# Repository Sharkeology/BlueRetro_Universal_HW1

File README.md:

# BlueRetro Universal HW1
A basic board meant to be used with the [BlueRetro project](https://github.com/darthcloud/BlueRetro) to simplify basic “HW1” internal installation in various supported consoles. Including onboard level shifting 3.3v regulation for consoles which don’t provide it.

### Bill of Materials
- [ESP-WROOM-32 Module](https://www.espressif.com/sites/default/files/documentation/esp32-wroom-32_datasheet_en.pdf)
- 2 x [TXS0108E 8-Bit Bi-directional, Level-Shifting, Voltage Translator](https://www.ti.com/lit/ds/symlink/txs0108e.pdf)
- 0805 1kΩ Pull-up Resistor for TXS0108E
- [AMS1117-3.3 3.3V 1A Low Dropout Voltage Regulator](http://www.advanced-monolithic.com/pdf/ds1117.pdf)
- 2 x 0805 Decoupling Capacitors for AMS1117 (I'm unsure of appropriate values, 1μF is what I used)

TXS0108EPWR Footprint and symbol courtesy of [SnapEDA](https://www.snapeda.com/parts/TXS0108EPWR/Texas%20Instruments/view-part/),
BlueRetro logo created by [HumbleBazooka](https://twitter.com/humblebazooka).

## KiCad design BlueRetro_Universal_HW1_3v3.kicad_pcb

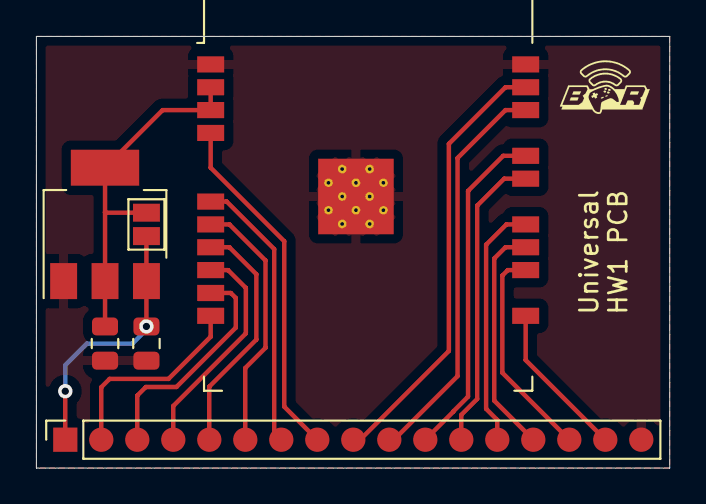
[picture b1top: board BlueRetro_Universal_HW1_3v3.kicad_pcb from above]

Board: 2 copper layers, 35.2 x 24.0 mm, 6 parts (0 on the bottom side), 18 nets.

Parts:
C1, C2: 1uF; C_0805_2012Metric
J1: Conn_01x17; PinSocket_1x17_P2.00mm_Vertical
JP1: SolderJumper_2_Open; SolderJumper-2_P1.3mm_Open_Pad1.0x1.5mm
U1: AMS1117-3.3; SOT-223-3_TabPin2
U2: ESP32-WROOM-32

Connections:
+3V3: C2.1, JP1.2 (B), U1.2 (VO), U2.2 (VDD), U2.3 (EN)
+5V: C1.1, J1.1, JP1.1 (A), U1.3 (VI)
GND: C1.2, C2.2, J1.17, U1.1 (GND), U2.1 (GND), U2.38 (GND), U2.39 (GND)
IO3: J1.11, U2.34 (RXD0/IO3)
IO5: J1.15, U2.29 (IO5)
IO16: J1.16, U2.27 (IO16)
IO18: J1.14, U2.30 (IO18)
IO19: J1.13, U2.31 (IO19)
IO21: J1.12, U2.33 (IO21)
IO22: J1.10, U2.36 (IO22)
IO23: J1.9, U2.37 (IO23)
IO25: J1.4, U2.10 (IO25)
IO26: J1.3, U2.11 (IO26)
IO27: J1.2, U2.12 (IO27)
IO32: J1.6, U2.8 (IO32)
IO33: J1.5, U2.9 (IO33)
IO35: J1.7, U2.7 (IO35)
IO36: J1.8, U2.4 (SENSOR_VP)

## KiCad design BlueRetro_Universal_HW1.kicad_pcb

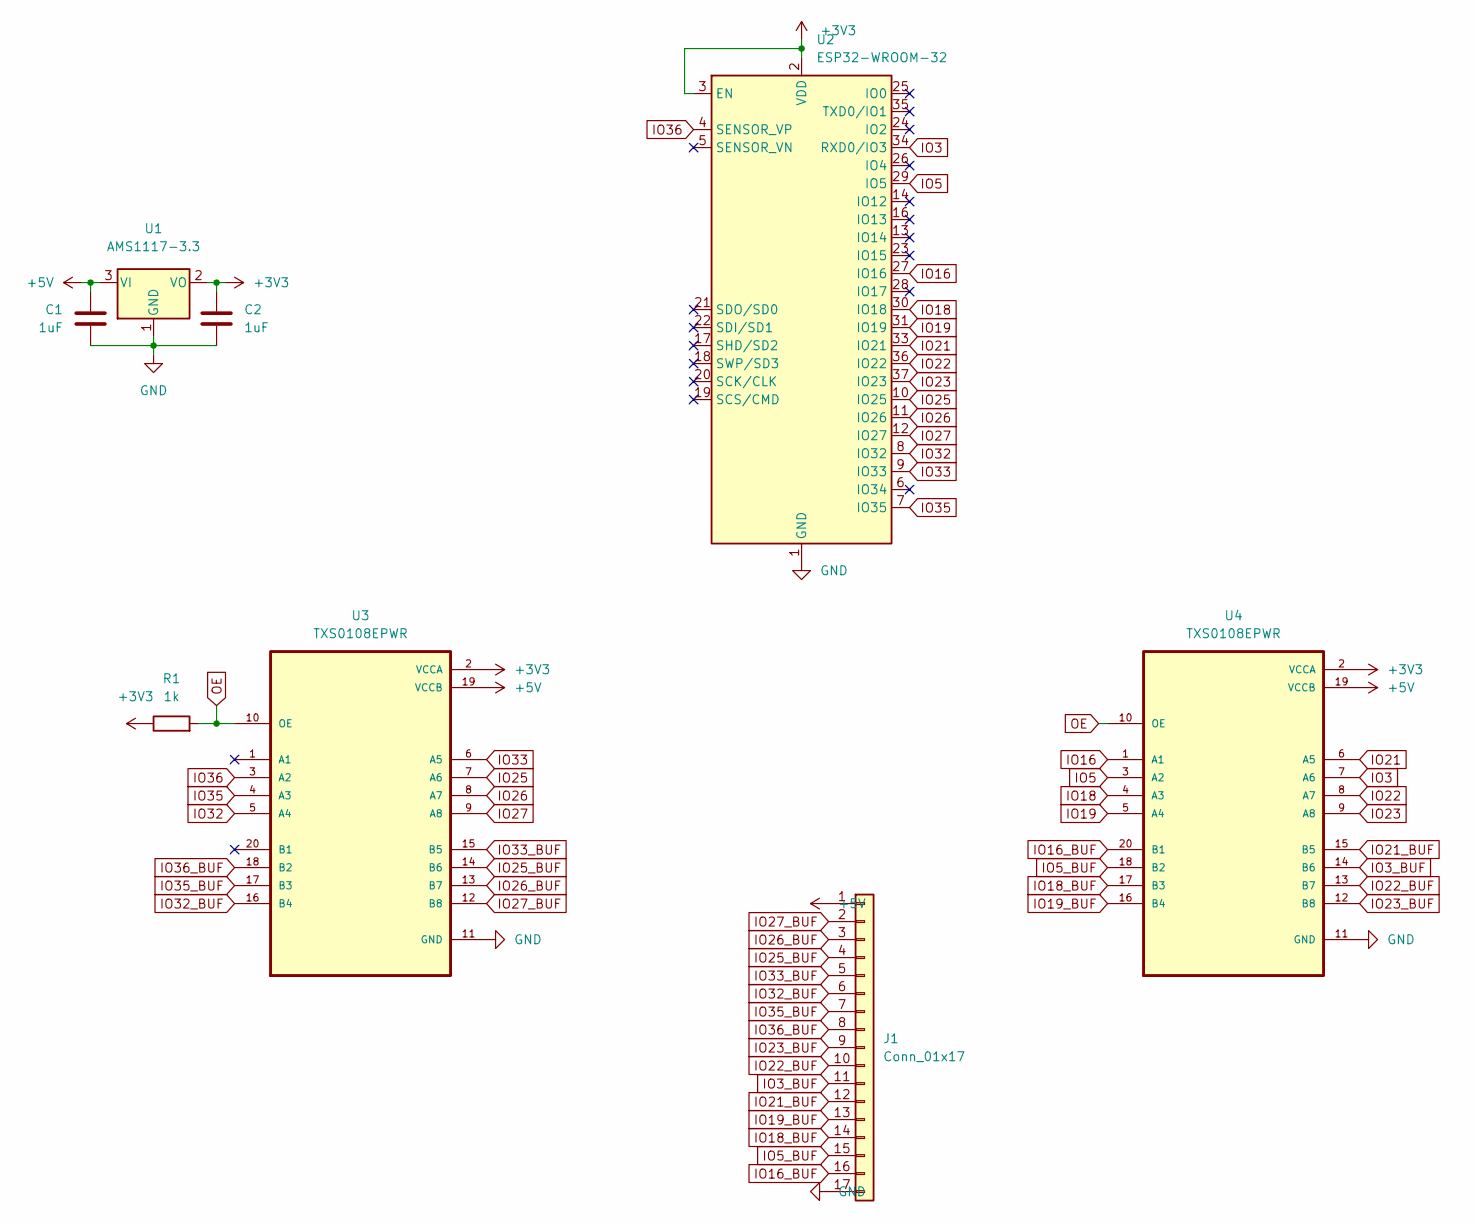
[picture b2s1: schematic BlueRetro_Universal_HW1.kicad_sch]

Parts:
C1, C2: 1uF; C_0805_2012Metric
J1: Conn_01x17; PinSocket_1x17_P2.00mm_Vertical
R1: 1k; R_0805_2012Metric
U1: AMS1117-3.3; SOT-223-3_TabPin2
U2: ESP32-WROOM-32
U3, U4: TXS0108EPWR; TSSOP-20_4.4x6.5mm_P0.65mm

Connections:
+3V3: C2.1, R1.1, U1.2 (VO), U2.2 (VDD), U2.3 (EN), U3.2 (VCCA), U4.2 (VCCA)
+5V: C1.1, J1.1, U1.3 (VI), U3.19 (VCCB), U4.19 (VCCB)
GND: C1.2, C2.2, J1.17, U1.1 (GND), U2.1 (GND), U2.15 (GND), U2.38 (GND), U2.39 (GND), U3.11 (GND), U4.11 (GND)
IO3: U2.34 (RXD0/IO3), U4.7 (A6)
IO3_BUF: J1.11, U4.14 (B6)
IO5: U2.29 (IO5), U4.3 (A2)
IO5_BUF: J1.15, U4.18 (B2)
IO16: U2.27 (IO16), U4.1 (A1)
IO16_BUF: J1.16, U4.20 (B1)
IO18: U2.30 (IO18), U4.4 (A3)
IO18_BUF: J1.14, U4.17 (B3)
IO19: U2.31 (IO19), U4.5 (A4)
IO19_BUF: J1.13, U4.16 (B4)
IO21: U2.33 (IO21), U4.6 (A5)
IO21_BUF: J1.12, U4.15 (B5)
IO22: U2.36 (IO22), U4.8 (A7)
IO22_BUF: J1.10, U4.13 (B7)
IO23: U2.37 (IO23), U4.9 (A8)
IO23_BUF: J1.9, U4.12 (B8)
IO25: U2.10 (IO25), U3.7 (A6)
IO25_BUF: J1.4, U3.14 (B6)
IO26: U2.11 (IO26), U3.8 (A7)
IO26_BUF: J1.3, U3.13 (B7)
IO27: U2.12 (IO27), U3.9 (A8)
IO27_BUF: J1.2, U3.12 (B8)
IO32: U2.8 (IO32), U3.5 (A4)
IO32_BUF: J1.6, U3.16 (B4)
IO33: U2.9 (IO33), U3.6 (A5)
IO33_BUF: J1.5, U3.15 (B5)
IO35: U2.7 (IO35), U3.4 (A3)
IO35_BUF: J1.7, U3.17 (B3)
IO36: U2.4 (SENSOR_VP), U3.3 (A2)
IO36_BUF: J1.8, U3.18 (B2)
OE: R1.2, U3.10 (OE), U4.10 (OE)

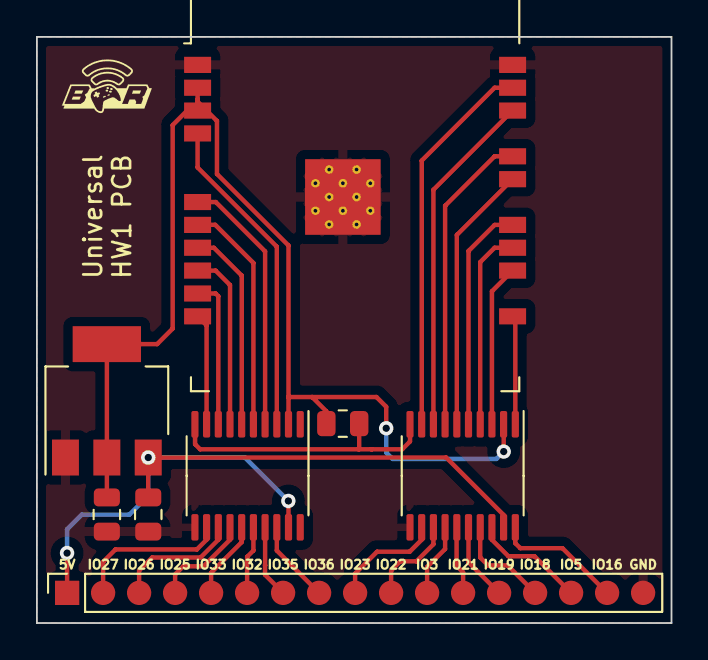
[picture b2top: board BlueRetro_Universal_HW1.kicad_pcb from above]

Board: 2 copper layers, 35.3 x 32.6 mm, 8 parts (0 on the bottom side), 34 nets.

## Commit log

2023-05-25 Create LICENSE
2023-05-25 Update README.md
    included attributions for footprints and logos
2023-06-07 Added 3v3 logic variant
    An additional board meant for more modern consoles whose controller buses use 3.3v logic has been uploaded. AMS1117 regulator still included for consoles without easily attainable 3.3v source (Sega D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
